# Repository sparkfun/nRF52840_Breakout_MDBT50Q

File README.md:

SparkFun Pro nRF52840 Mini - Bluetooth Development Board
========================================

[*SparkFun Pro nRF52840 Mini - Bluetooth Development Board (DEV-15025)*](https://www.sparkfun.com/products/15025)

<Basic description of the part.>

Repository Contents
-------------------

* **/Documentation** - Data sheets, additional product information
* **/Firmware** -- nRF5 SDK and Arduino firmware components
  * **/Arduino** -- Board definitions and variants for installing in the [nRF52 Arduino Core](https://github.com/adafruit/Adafruit_nRF52_Arduino)
  * **/nRF5_SDK** -- Board definitions for use in the nRF5 SDK.
* **/Hardware** - Eagle design files (.brd, .sch)
* **/Production** - Production panel files (.brd)

Documentation
--------------
* **[Hookup Guide](https://learn.sparkfun.com/tutorials/sparkfun-pro-nrf52840-mini-hookup-guide)** - Basic hookup guide for the Pro nrf52840.

Product Versions
----------------
* [DEV-15025](https://www.sparkfun.com/products/15025)- The SparkFun Pro nRF52840 Mini is a breakout and development board for Nordic Semiconductor’s nRF52840 – a powerful combination of ARM Cortex-M4 CPU and 2.4 GHz Bluetooth radio. With the nRF52840 at the heart of your project, you’ll be presented with a seemingly endless list of project-possibilities.

License Information
-------------------

This product is _**open source**_! 

Please review the LICENSE.md file for license information.

If you have any questions or concerns on licensing, please visit the [SparkFun Forum](https://forum.sparkfun.com/index.php) and post a topic.

Distributed as-is; no warranty is given.

- Your friends at SparkFun.

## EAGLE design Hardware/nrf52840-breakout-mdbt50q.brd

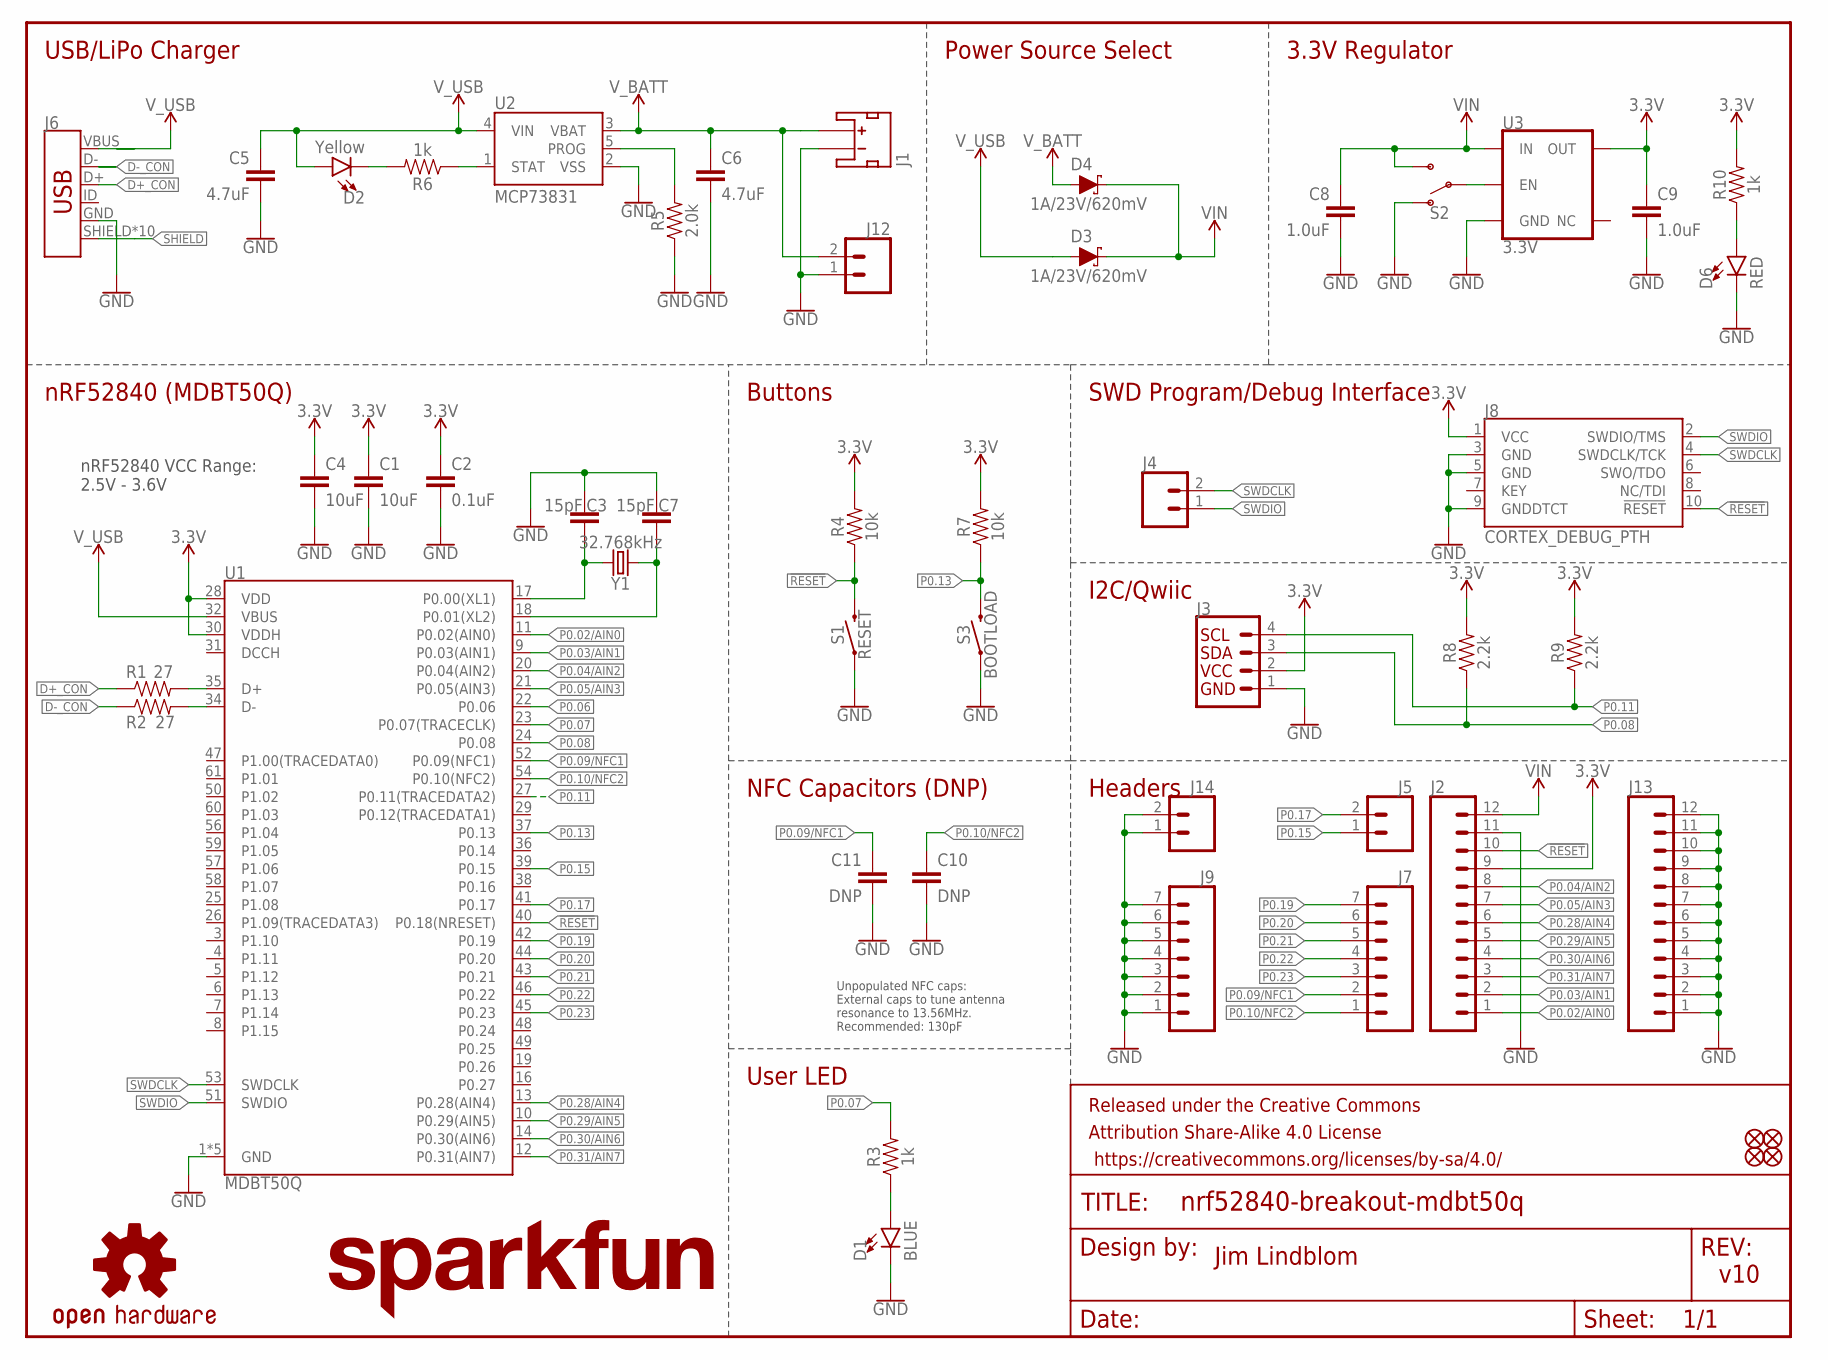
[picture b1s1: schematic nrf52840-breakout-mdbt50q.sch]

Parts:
C1, C4: 10uF; 0603
C2: 0.1uF; 0603
C3, C7: 15pF; 0603
C5, C6: 4.7uF; 0603
C8, C9: 1.0uF; 0603
C10, C11: DNP; 0603
D1: BLUE; LED-0603
D2: Yellow; LED-0603
D3, D4: 1A/23V/620mV; SOD-323
D6: RED; LED-0603
FD1, FD2, FD3, FD4: FIDUCIALUFIDUCIAL; FIDUCIAL-MICRO
FRAME1: FRAME-LETTER; CREATIVE_COMMONS
J1: JST_2MM_MALESMD; JST-2-SMD
J2, J13: CONN_12NO_SILK; 1X12_NO_SILK
J3: QWIIC_CONNECTORJS-1MM; 1X04_1MM_RA
J4, J5, J12, J14: CONN_021X02_NO_SILK; 1X02_NO_SILK
J6: USB_MICRO-B_HALF_PTH_MILL; USB-MICROB-PTH-MILL
J7, J9: CONN_07NO_SILK; 1X07_NO_SILK
J8: CORTEX_DEBUG_PTH; 2X5-PTH-1.27MM
LOGO1: SFE_LOGO_NAME.2_INCH; SFE_LOGO_NAME_.2
LOGO2: OSHW-LOGOS; OSHW-LOGO-S
R1, R2: 27; 0603
R3, R6, R10: 1k; 0603
R4, R7: 10k; 0603
R5: 2.0k; 0603
R8, R9: 2.2k; 0603
S1: RESET; TACTILE_SWITCH_SMD_RIGHT_ANGLE
S2: SWITCH-SPDT-SMD-RIGHT-ANGLE; SWITCH_SPST_SMD_A
S3: BOOTLOAD; TACTILE_SWITCH_SMD_RIGHT_ANGLE
U1: MDBT50Q
U2: MCP73831; SOT23-5
U3: 3.3V; SOT23-5
Y1: 32.768kHz; CRYSTAL-SMD-3.2X1.5MM

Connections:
3.3V: C1.1, C2.1, C4.1, C9.1, J2.9, J3.2, J8.1 (VCC), R4.2, R7.2, R8.2, R9.2, R10.2, U1.28 (VDD), U1.30 (VDDH), U3.5 (OUT)
!RESET: J2.10, J8.10 (!RESET), R4.1, S1.2, U1.40 (P0.18(NRESET))
D+: R1.2, U1.35 (D+)
D+_CON: J6.D+, R1.1
D-: R2.2, U1.34 (D-)
D-_CON: J6.D-, R2.1
GND: C1.2, C2.2, C3.1, C4.2, C5.2, C6.2, C7.1, C8.2, C9.2, C10.2, C11.2, D1.C, D6.C, J1.1 (-), J2.11, J3.1, J6.GND, J8.3 (GND), J8.5 (GND), J8.9 (GNDDTCT), J9.1, J9.2, J9.3, J9.4, J9.5, J9.6, J9.7, J12.1, J13.1, J13.2, J13.3, J13.4, J13.5, J13.6, J13.7, J13.8, J13.9, J13.10, J13.11, J13.12, J14.1, J14.2, R5.1, S1.1, S2.1 (O), S3.1, U1.1 (GND), U1.2 (GND), U1.15 (GND), U1.33 (GND), U1.55 (GND), U2.2 (VSS), U3.2 (GND)
unnamed: R5.2, U2.5 (PROG)
unnamed: D2.C, R6.2
unnamed: R6.1, U2.1 (STAT)
unnamed: D1.A, R3.1
unnamed: D6.A, R10.1
P0.02/AIN0: J2.1, U1.11 (P0.02(AIN0))
P0.03/AIN1: J2.2, U1.9 (P0.03(AIN1))
P0.04/AIN2: J2.8, U1.20 (P0.04(AIN2))
P0.05/AIN3: J2.7, U1.21 (P0.05(AIN3))
P0.06: U1.22 (P0.06)
P0.07: R3.2, U1.23 (P0.07(TRACECLK))
P0.08: J3.3, R8.1, U1.24 (P0.08)
P0.09/NFC1: C11.1, J7.2, U1.52 (P0.09(NFC1))
P0.10/NFC2: C10.1, J7.1, U1.54 (P0.10(NFC2))
P0.11: J3.4, R9.1, U1.27 (P0.11(TRACEDATA2))
P0.13: R7.1, S3.2, U1.37 (P0.13)
P0.15: J5.1, U1.39 (P0.15)
P0.17: J5.2, U1.41 (P0.17)
P0.19: J7.7, U1.42 (P0.19)
P0.20: J7.6, U1.44 (P0.20)
P0.21: J7.5, U1.43 (P0.21)
P0.22: J7.4, U1.46 (P0.22)
P0.23: J7.3, U1.45 (P0.23)
P0.28/AIN4: J2.6, U1.13 (P0.28(AIN4))
P0.29/AIN5: J2.5, U1.10 (P0.29(AIN5))
P0.30/AIN6: J2.4, U1.14 (P0.30(AIN6))
P0.31/AIN7: J2.3, U1.12 (P0.31(AIN7))
SHIELD: J6.SHIELD, J6.SHIELD2 (SHIELD), J6.SHIELD3 (SHIELD), J6.SHIELD4 (SHIELD), J6.SHIELD5 (SHIELD), J6.SHIELD6 (SHIELD), J6.SHIELD7 (SHIELD), J6.SHIELD8 (SHIELD), J6.SHIELD9 (SHIELD), J6.SHIELD10 (SHIELD)
SWDCLK: J4.2, J8.4 (SWDCLK/TCK), U1.53 (SWDCLK)
SWDIO: J4.1, J8.2 (SWDIO/TMS), U1.51 (SWDIO)
VIN: C8.1, D3.C, D4.C, J2.12, S2.3 (S), U3.1 (IN)
VREG_EN: S2.2, U3.3 (EN)
V_BATT: C6.1, D4.A, J1.2 (+), J12.2, U2.3 (VBAT)
V_USB: C5.1, D2.A, D3.A, J6.VBUS, U1.32 (VBUS), U2.4 (VIN)
XL1: C3.2, U1.17 (P0.00(XL1)), Y1.P$2 (2)
XL2: C7.2, U1.18 (P0.01(XL2)), Y1.P$1 (1)

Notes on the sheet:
v10
Jim Lindblom
SWD Program/Debug Interface
I2C/Qwiic
Headers
NFC Capacitors (DNP)
Buttons
User LED
nRF52840 (MDBT50Q)
USB/LiPo Charger
Power Source Select
3.3V Regulator
Unpopulated NFC caps: External caps to tune antenna resonance to 13.56MHz. Recommended: 130pF
nRF52840 VCC Range: 2.5V - 3.6V

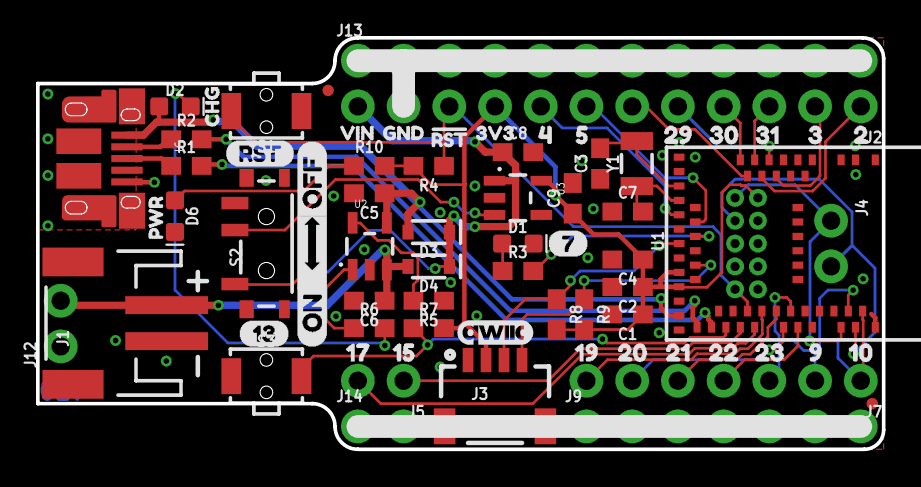
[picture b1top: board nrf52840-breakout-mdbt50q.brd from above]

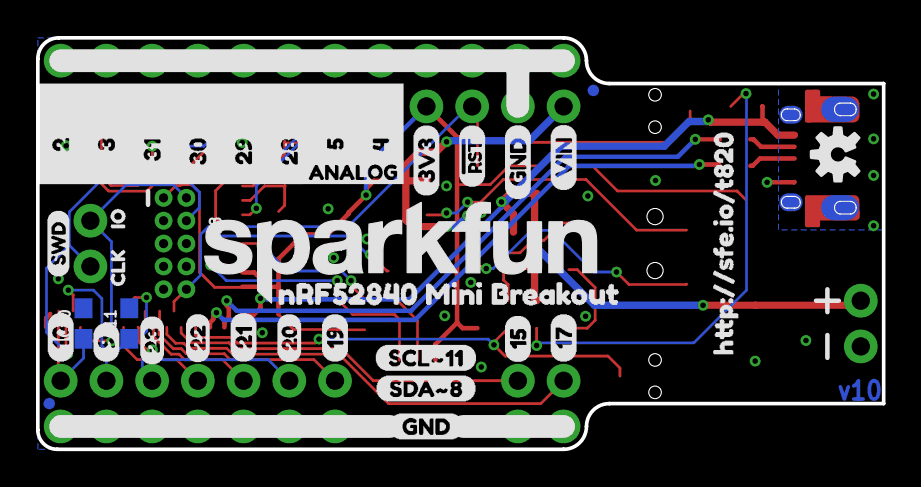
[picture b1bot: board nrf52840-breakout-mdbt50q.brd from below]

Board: 2 copper layers, 47.0 x 22.9 mm, 110 parts (37 on the bottom side), 42 nets.

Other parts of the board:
U$1: 3V316
U$2: 130
U$3: RST19
U$4: ON1
U$5: CHG26
U$6: PWR27
U$7: GND17
U$8: QWIIC#LOGO#JPG
U$9: 20
U$10: 31
U$11: 292
U$12: 313
U$13: 3V30
U$14: 285
U$15: 521
U$16: 421
U$17: HTTP###SFE#IO#T8200
U$18: #RST6
U$19: GND7
U$20: VIN8
U$21: 1022
U$22: 916
U$23: 2111
U$24: 1912
U$25: 1713
U$26: 1522
U$27: VIN19
U$28: 70
U$29: NRF52840_MINI_BREAKOUT0
U$30: GND6
U$31: 27
U$32: 36
U$33: SWD0
U$34: 315
U$35: 300
U$36: 301
U$37: 293
U$38: 108
U$39: 51
U$40: 40
U$41: 97
U$42: 236
U$43: 200
U$44: 225
U$45: 221
U$46: 214
U$47: 203
U$48: 192
U$49: 151
U$50: 170
U$51: RST1
U$52: ANALOG2
U$53: 232
U$54: SCL#114
U$55: SDA#83
U$56: IO2
U$57: CLK1
U$58: OFF2

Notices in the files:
parts and their libraries:
SparkFun-Aesthetics: Licensing: Creative Commons ShareAlike 4.0 International - https://creativecommons.org/licenses/by-sa/4.0
SparkFun-Aesthetics: Released under the Creative Commons Attribution Share-Alike 4.0 License
SparkFun-Aesthetics: https://creativecommons.org/licenses/by-sa/4.0
